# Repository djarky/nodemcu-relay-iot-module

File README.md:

# nodemcu-relay-iot-module
friendly usage and config nodemcu to conect lights offine (local ip) and online ( arduino cluoud / Blynk IoT)

- upload code via arduinoide
- conect wifi to ESP8266config
- navgegate to ip (tipical 192.168.4.1 )
- configuration page ip/config http://192.168.4.1/config
- help http://192.168.4.1/help

if use arduino cloud (not recomended ) flash iot_luces_v4.ino 
-
if use Blynk IoT (very recomened) flash iot_luces_v6.ino or later 
-

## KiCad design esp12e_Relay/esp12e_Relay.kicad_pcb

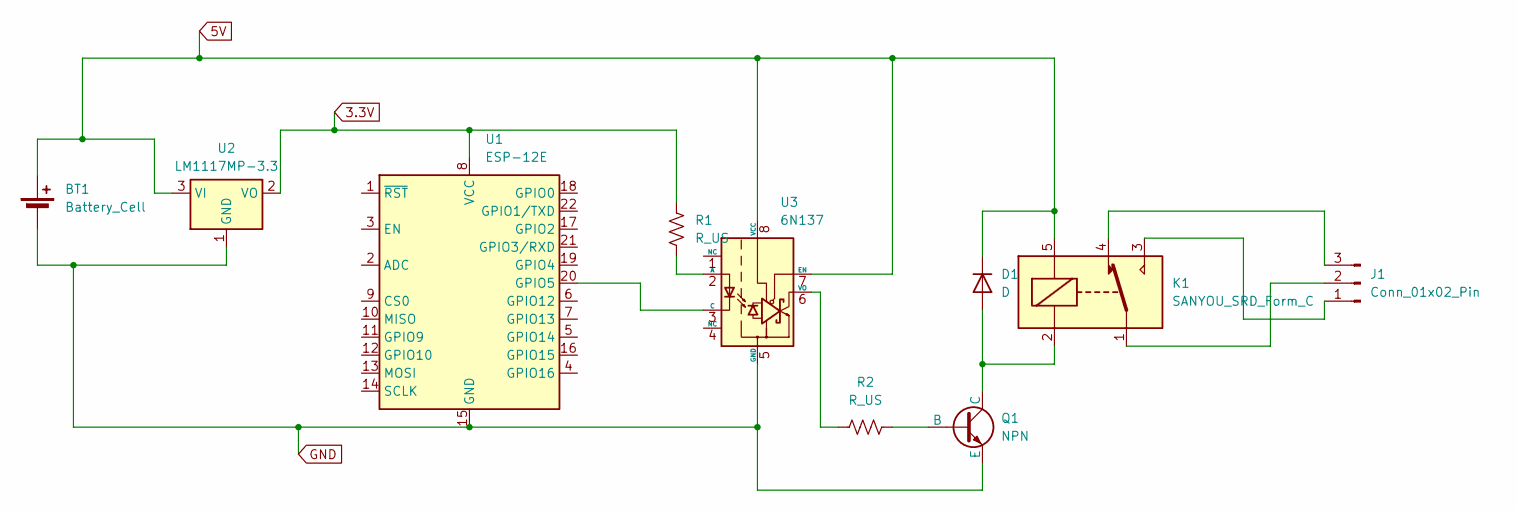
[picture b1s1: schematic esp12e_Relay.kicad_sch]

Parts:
BT1: Battery_Cell; BarrelJack_CUI_PJ-079BH_Horizontal
D1: D; D_DO-35_SOD27_P10.16mm_Horizontal
J1: Conn_01x02_Pin; SolderWire-2.5sqmm_1x03_P7.2mm_D2.4mm_OD3.6mm
K1: SANYOU_SRD_Form_C; Relay_SPDT_SANYOU_SRD_Series_Form_C
Q1: NPN; TO-92_HandSolder
R1, R2: R_US; R_Axial_DIN0207_L6.3mm_D2.5mm_P15.24mm_Horizontal
U1: ESP-12E
U2: LM1117MP-3.3; SOT-223-3_TabPin2
U3: 6N137; DIP-8_W7.62mm

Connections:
3.3V: R1.1, U1.8 (VCC), U2.2 (VO)
5V: BT1.1 (+), D1.1 (K), K1.5, U2.3 (VI), U3.7 (EN), U3.8 (VCC)
GND: BT1.2 (-), Q1.3 (E), U1.15 (GND), U2.1 (GND), U3.5 (GND)
unnamed: D1.2 (A), K1.2, Q1.1 (C)
unnamed: J1.1, K1.3
unnamed: J1.2, K1.1
unnamed: J1.3, K1.4
unnamed: Q1.2 (B), R2.1
unnamed: U1.20 (GPIO5), U3.3 (C)
unnamed: R1.2, U3.2 (A)
unnamed: R2.2, U3.6 (VO)

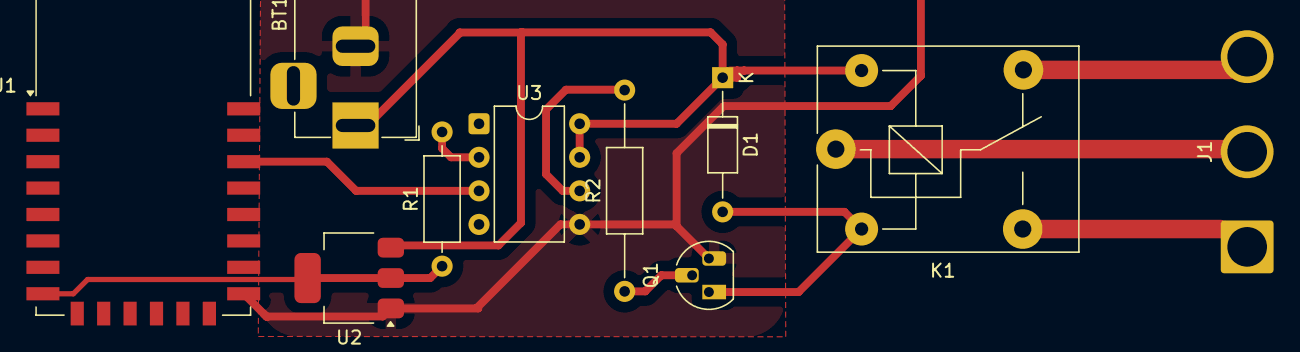
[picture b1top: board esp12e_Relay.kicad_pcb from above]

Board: 2 copper layers, 10 parts (0 on the bottom side), 11 nets.

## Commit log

2025-06-28 Rename Captura de pantalla 2025-06-25 184315.png to gui.png
2025-06-28 Rename Captura de pantalla 2025-06-28 184033.png to config.png
2026-02-17 Add initial IoT light control functionality
